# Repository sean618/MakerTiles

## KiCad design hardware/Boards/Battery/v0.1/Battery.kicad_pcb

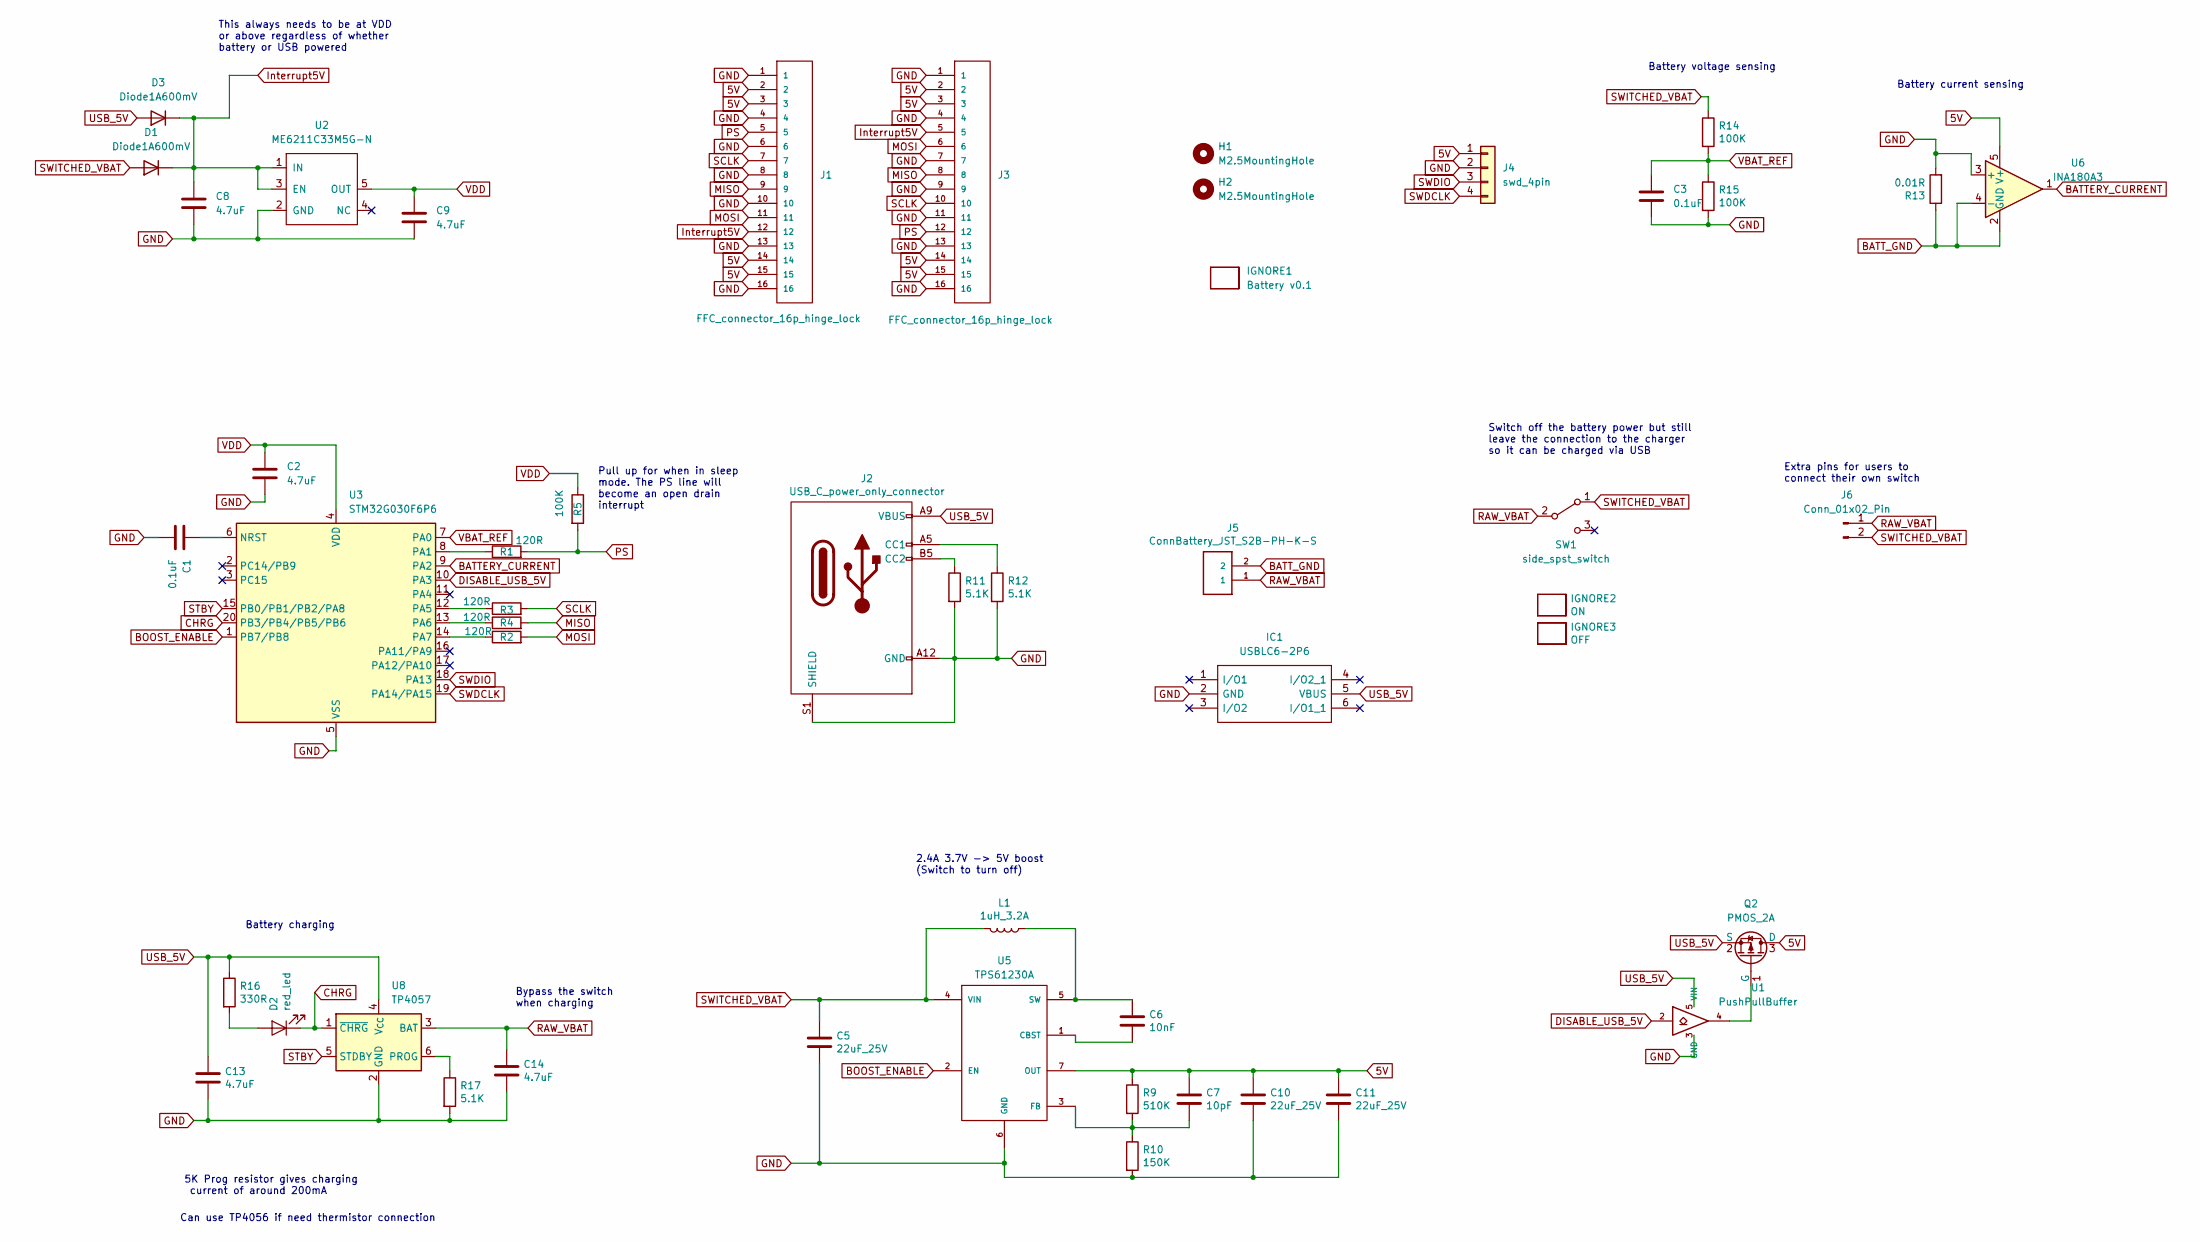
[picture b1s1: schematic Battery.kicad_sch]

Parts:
C1, C3: 0.1uF; C_0402_1005Metric
C2, C8, C9, C13, C14: 4.7uF; C_0402_1005Metric
C5, C10, C11: 22uF_25V; C_0805_2012Metric
C6: 10nF; C_0402_1005Metric
C7: 10pF; C_0402_1005Metric
D1, D3: Diode1A600mV; D_SOD-323
D2: red_led; LED_SML-D12D1WT86; Manufacturer_Part_Number SML-D12D1WT86
H1, H2: M2.5MountingHole; MountingHole_2.7mm_M2.5_ISO7380
IC1: USBLC6-2P6; Manufacturer_Part_Number USBLC6-2P6
IGNORE1: Battery v0.1; BoardText
IGNORE2: ON; BoardText
IGNORE3: OFF; BoardText
J1, J3: FFC_connector_16p_hinge_lock
J2: USB_C_power_only_connector; USB_C_Receptacle_power_only_6P
J4: swd_4pin; swd_header
J5: ConnBattery_JST_S2B-PH-K-S; JST_PH_S2B-PH-K_1x02_P2.00mm_Horizontal; Manufacturer_Part_Number S2B-PH-K-S
J6: Conn_01x02_Pin; PinHeader_1x02_P2.54mm_Vertical
L1: 1uH_3.2A; L_1008_2520Metric
Q2: PMOS_2A; SOT-23
R1, R2, R3, R4: 120R; R_0402_1005Metric
R5, R14, R15: 100K; R_0402_1005Metric
R9: 510K; R_0402_1005Metric
R10: 150K; R_0402_1005Metric
R11, R12, R17: 5.1K; R_0402_1005Metric
R13: 0.01R; R_0603_1608Metric_Pad0.98x0.95mm_HandSolder
R16: 330R; R_0402_1005Metric
SW1: side_spst_switch
U1: PushPullBuffer; 74LVC1G07GW
U2: ME6211C33M5G-N; SOT-23-5
U3: STM32G030F6P6; TSSOP-20_4.4x6.5mm_P0.65mm
U5: TPS61230A
U6: INA180A3; SOT-23-5
U8: TP4057; SOT-23-6

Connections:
5V: C7.1, C10.1, C11.1, J1.2, J1.3, J1.14, J1.15, J3.2, J3.3, J3.14, J3.15, J4.1, Q2.3 (D), R9.1, U5.7 (OUT), U6.5 (V+)
BATTERY_CURRENT: U3.9 (PA2), U6.1
BATT_GND: J5.2, R13.1, U6.2 (GND), U6.4 (-)
BOOST_ENABLE: U3.1 (PB7/PB8), U5.2 (EN)
CHRG: D2.1 (K), U3.20 (PB3/PB4/PB5/PB6), U8.1 (~CHRG)
DISABLE_USB_5V: U1.2, U3.10 (PA3)
GND: C1.2, C2.2, C3.2, C5.2, C8.2, C9.2, C10.2, C11.2, C13.2, C14.2, IC1.2 (GND), J1.1, J1.4, J1.6, J1.8, J1.10, J1.13, J1.16, J2.A12 (GND), J2.B12 (GND), J2.S1 (SHIELD), J3.1, J3.4, J3.7, J3.9, J3.11, J3.13, J3.16, J4.2, R10.2, R11.2, R12.2, R13.2, R15.2, R17.2, U1.3 (GND), U2.2 (GND), U3.5 (VSS), U5.6 (GND), U6.3 (+), U8.2 (GND)
Interrupt5V: C8.1, D1.1 (K), D3.1 (K), J1.12, J3.5, U2.1 (IN), U2.3 (EN)
MISO: J1.9, J3.8, R4.2
MOSI: J1.11, J3.6, R2.2
unnamed: D2.2 (A), R16.2
unnamed: J2.A5 (CC1), R12.1
unnamed: J2.B5 (CC2), R11.1
unnamed: Q2.1 (G), U1.4
unnamed: C1.1, U3.6 (NRST)
unnamed: R1.1, U3.8 (PA1)
unnamed: R3.1, U3.12 (PA5)
unnamed: R4.1, U3.13 (PA6)
unnamed: R2.1, U3.14 (PA7)
unnamed: C6.2, U5.1 (CBST)
unnamed: C7.2, R9.2, R10.1, U5.3 (FB)
unnamed: C6.1, L1.1, U5.5 (SW)
unnamed: R17.1, U8.6 (PROG)
PS: J1.5, J3.12, R1.2, R5.2
RAW_VBAT: C14.1, J5.1, J6.1, SW1.2 (B), U8.3 (BAT)
SCLK: J1.7, J3.10, R3.2
STBY: U3.15 (PB0/PB1/PB2/PA8), U8.5 (STDBY)
SWDCLK: J4.4, U3.19 (PA14/PA15)
SWDIO: J4.3, U3.18 (PA13)
SWITCHED_VBAT: C5.1, D1.2 (A), J6.2, L1.2, R14.1, SW1.1 (A), U5.4 (VIN)
USB_5V: C13.1, D3.2 (A), IC1.5 (VBUS), J2.A9 (VBUS), J2.B9 (VBUS), Q2.2 (S), R16.1, U1.5 (VIN), U8.4 (V_{CC})
VBAT_REF: C3.1, R14.2, R15.1, U3.7 (PA0)
VDD: C2.1, C9.1, R5.1, U2.5 (OUT), U3.4 (VDD)

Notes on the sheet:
Battery current sensing
This always needs to be at VDD or above regardless of whether battery or USB powered
Can use TP4056 if need thermistor connection
Bypass the switch when charging
Battery charging
Extra pins for users to connect their own switch
Switch off the battery power but still leave the connection to the charger so it can be charged via USB
Pull up for when in sleep mode. The PS line will become an open drain interrupt
Battery voltage sensing
5K Prog resistor gives charging current of around 200mA
2.4A 3.7V -> 5V boost (Switch to turn off)

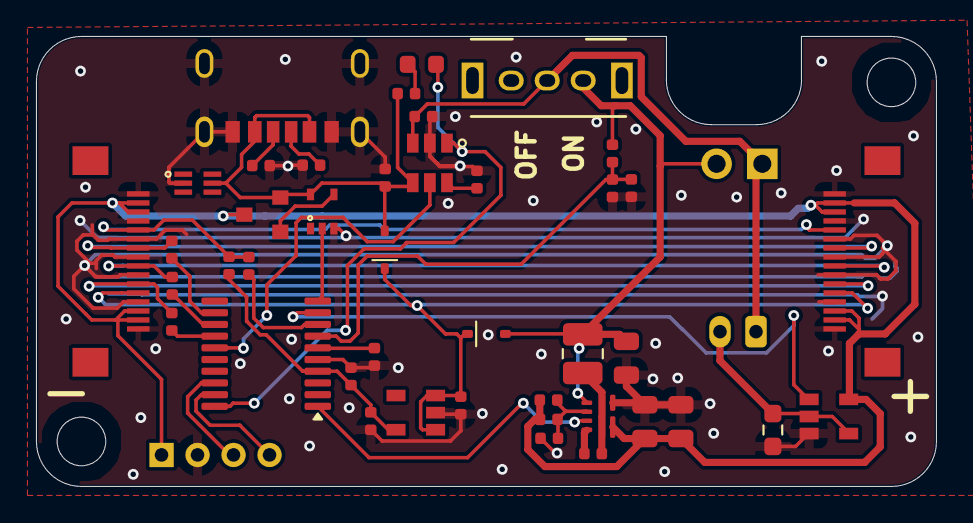
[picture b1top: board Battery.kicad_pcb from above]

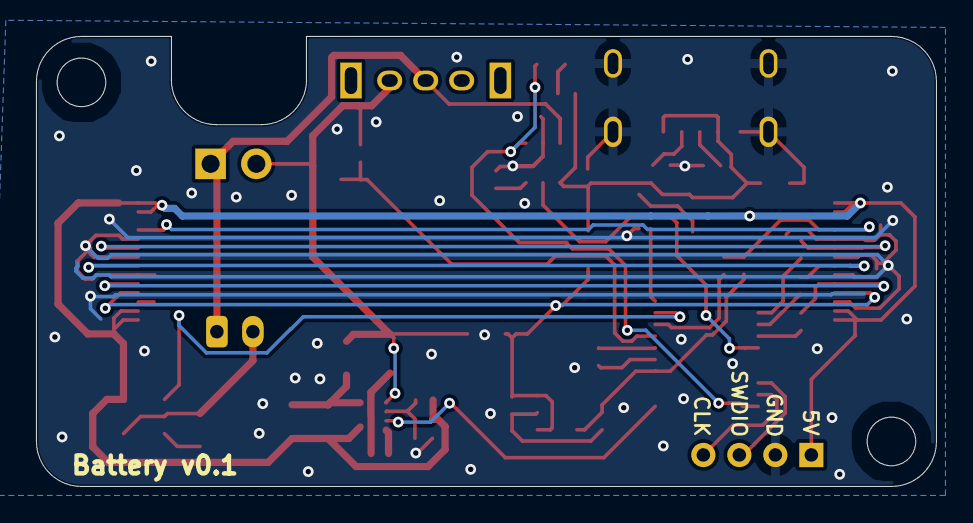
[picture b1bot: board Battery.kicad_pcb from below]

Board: 4 copper layers, 50.0 x 25.0 mm, 50 parts (2 on the bottom side), 33 nets.

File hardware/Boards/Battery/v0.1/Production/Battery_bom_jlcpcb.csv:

Comment,Designator,Footprint,LCSC Part Number
4.7uF,"C9,C13,C14,C8,C2",C_0402_1005Metric,C23733
FFC_connector_16p_hinge_lock,"J1,J3",FFC_connector_16p_hinge_lock,C262665
0.01R,R13,R_0603_1608Metric_Pad0.98x0.95mm_HandSolder,C158899
Diode1A600mV,"D1,D3",D_SOD-323,C191023
22uF_25V,"C10,C5,C11",C_0805_2012Metric,C602037
red_led,D2,LED_SML-D12D1WT86,C2286
side_spst_switch,SW1,side_spst_switch,C431548
10pF,C7,C_0402_1005Metric,C32949
ConnBattery_JST_S2B-PH-K-S,J5,JST_PH_S2B-PH-K_1x02_P2.00mm_Horizontal,C173752
USB_C_power_only_connector,J2,USB_C_Receptacle_power_only_6P,C283540
INA180A3,U6,SOT-23-5,C122882
USBLC6-2P6,IC1,USBLC6-2P6,C2827693
TP4057,U8,SOT-23-6,C5380673
TPS61230A,U5,TPS61230A,C376005
ME6211C33M5G-N,U2,SOT-23-5,C81233
150K,R10,R_0402_1005Metric,C25755
510K,R9,R_0402_1005Metric,C11616
100K,"R5,R15,R14",R_0402_1005Metric,C25741
330R,R16,R_0402_1005Metric,C25104
120R,"R2,R3,R4,R1",R_0402_1005Metric,C25079
PMOS_2A,Q2,SOT-23,C306862
STM32G030F6P6,U3,TSSOP-20_4.4x6.5mm_P0.65mm,C529330
5.1K,"R12,R17,R11",R_0402_1005Metric,C25905
1uH_3.2A,L1,L_1008_2520Metric,C315711
0.1uF,"C1,C3",C_0402_1005Metric,C1525
10nF,C6,C_0402_1005Metric,C15195
PushPullBuffer,U1,74LVC1G07GW,C426705

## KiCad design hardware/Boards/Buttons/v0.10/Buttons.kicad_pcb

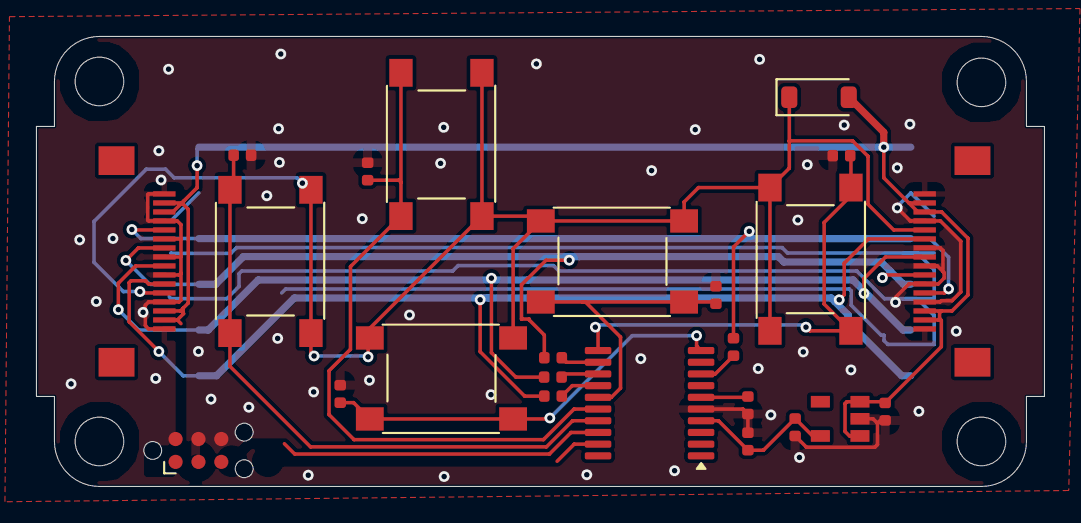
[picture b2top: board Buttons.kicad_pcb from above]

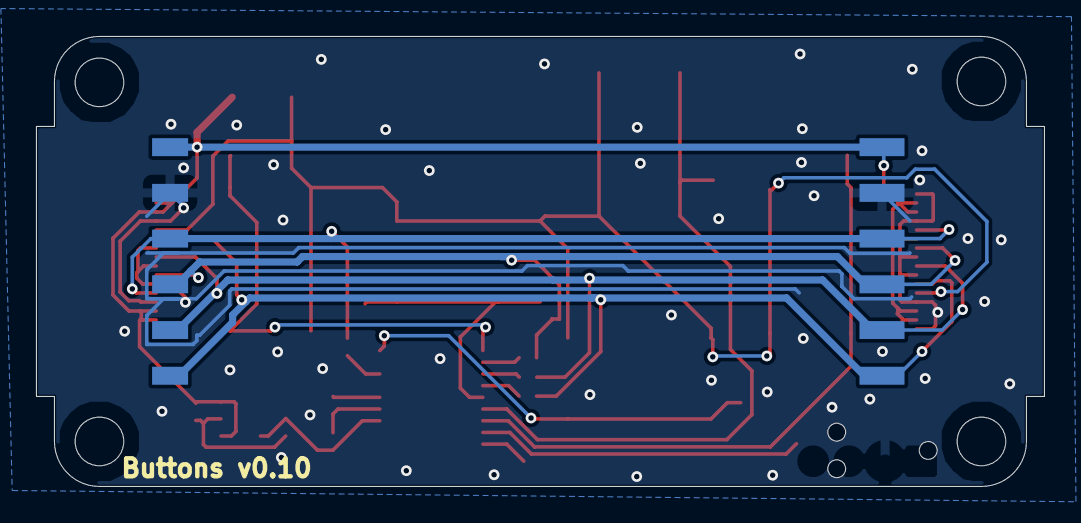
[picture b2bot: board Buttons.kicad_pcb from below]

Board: 2 copper layers, 56.0 x 25.0 mm, 31 parts (2 on the bottom side), 20 nets.

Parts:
C1: 0.1uF; C_0402_1005Metric
C2, C8, C9: 4.7uF; C_0402_1005Metric
D2: 1N4148W; D_SOD-123
H1, H2, H3, H4: M2.5MountingHole; MountingHole_2.7mm_M2.5_ISO7380
IGNORE1: Buttons v0.10; BoardText
J1: 01x06_2.54mm_Male
J2: 01x06_2.54mm_Female
J3, J5: FFC_connector_16p_hinge_lock
J4: Conn_ARM_SWD_TagConnect_TC2030-NL; Tag-Connect_TC2030-IDC-NL_2x03_P1.27mm_Vertical
R1, R2, R3, R4: 75R; R_0402_1005Metric
R5, R6, R7, R8, R9: 10K; R_0402_1005Metric
SW1, SW2, SW3, SW4, SW6: button_6x6x7; SW_SPST_PTS645
U2: ME6211C33M5G-N; SOT-23-5
U3: STM32G030F6P6; TSSOP-20_4.4x6.5mm_P0.65mm

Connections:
5V: C8.1, D2.2 (A), J1.1, J2.6, J3.2, J3.3, J3.14, J3.15, J5.2, J5.3, J5.14, J5.15, U2.1 (IN), U2.3 (EN)
GND: C1.2, C2.2, C8.2, C9.2, J1.2, J2.5, J3.1, J3.4, J3.6, J3.8, J3.10, J3.13, J3.16, J4.5 (GND), J5.1, J5.4, J5.6, J5.8, J5.10, J5.13, J5.16, R5.1, R6.1, R7.1, R8.1, R9.1, U2.2 (GND), U3.5 (VSS)
Interrupt5V: D2.1 (K), J3.12, J5.12, SW1.2, SW2.2, SW3.2, SW4.2, SW6.2
MISO: J1.5, J2.2, J3.9, J5.9, R4.2
MOSI: J1.6, J2.1, J3.11, J5.11, R2.2
NRST: C1.1, J4.3 (~RESET), U3.6 (NRST)
unnamed: R1.1, U3.8 (PA1)
unnamed: R3.1, U3.12 (PA5)
unnamed: R4.1, U3.13 (PA6)
unnamed: R2.1, U3.14 (PA7)
PS: J1.3, J2.4, J3.5, J5.5, R1.2
SCLK: J1.4, J2.3, J3.7, J5.7, R3.2
SW1: R5.2, SW2.1, U3.16 (PA11/PA9)
SW2: R6.2, SW1.1, U3.17 (PA12/PA10)
SW3: R7.2, SW6.1, U3.11 (PA4)
SW4: R9.2, SW3.1, U3.15 (PB0/PB1/PB2/PA8)
SW5: R8.2, SW4.1, U3.10 (PA3)
SWDCLK: J4.4 (SWCLK), U3.19 (PA14/PA15)
SWDIO: J4.2 (SWDIO), U3.18 (PA13)
VDD: C2.1, C9.1, J4.1 (VCC), U2.5 (OUT), U3.4 (VDD)

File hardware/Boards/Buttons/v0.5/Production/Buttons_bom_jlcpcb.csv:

Comment,Designator,Footprint,LCSC Part Number
4.7uF,"C9,C8,C2",C_0402_1005Metric,C23733
FFC_connector_16p_hinge_lock,"J5,J3",FFC_connector_16p_hinge_lock,C262665
button_6x6x7,"SW1,SW2,SW4,SW3,SW6",SW_SPST_PTS645,C381064
10K,"R9,R6,R8,R5,R7",R_0402_1005Metric,C25744
ME6211C33M5G-N,U2,SOT-23-5,C81233
75R,"R2,R3,R4,R1",R_0402_1005Metric,C25133
STM32G030F6P6,U3,TSSOP-20_4.4x6.5mm_P0.65mm,C529330
0.1uF,C1,C_0402_1005Metric,C1525
1N4148W,D2,D_SOD-123,C81598
01x06_2.54mm_Male,J1,01x06_2.54mm_Male,C5242199
01x06_2.54mm_Female,J2,01x06_2.54mm_Female,C5142239

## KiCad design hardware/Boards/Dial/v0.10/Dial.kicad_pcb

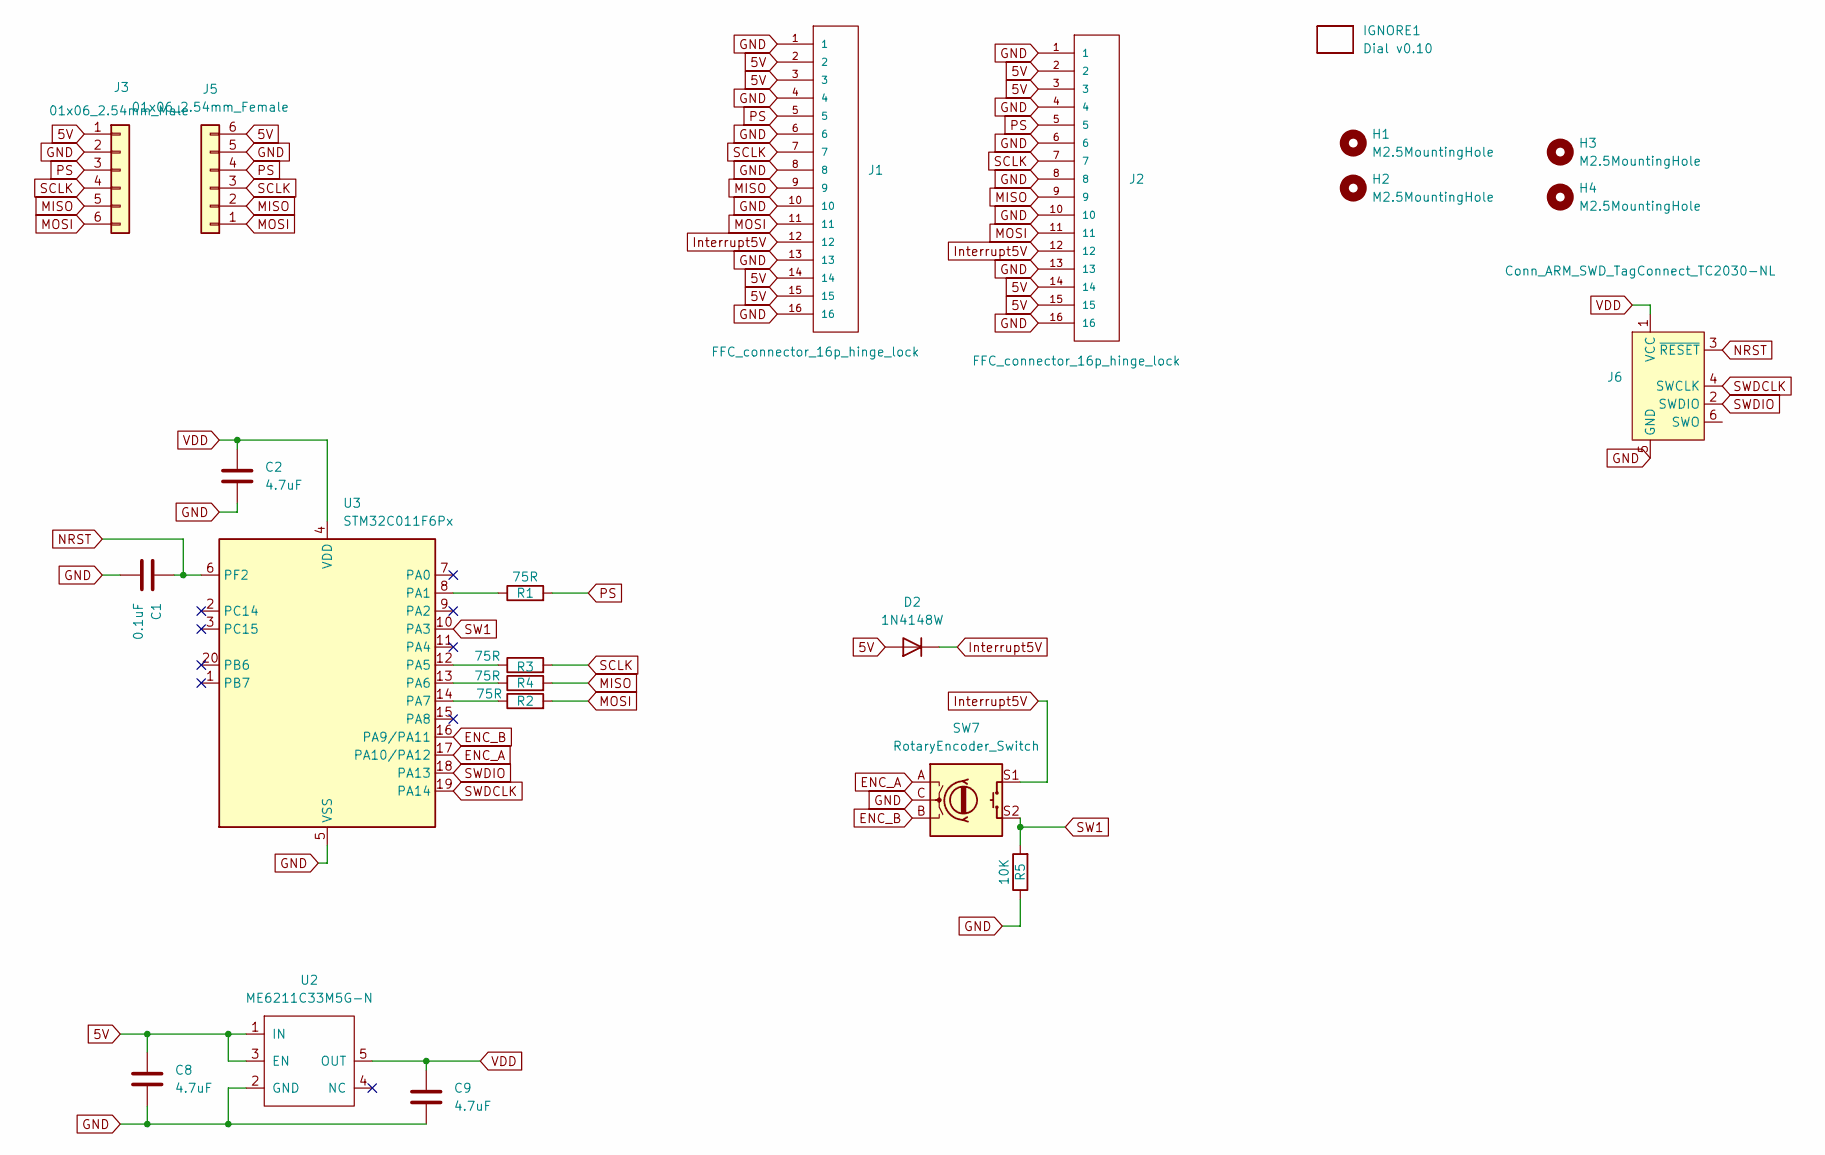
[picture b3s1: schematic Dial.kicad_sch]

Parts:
C1: 0.1uF; C_0402_1005Metric
C2, C8, C9: 4.7uF; C_0402_1005Metric
D2: 1N4148W; D_SOD-123
H1, H2, H3, H4: M2.5MountingHole; MountingHole_2.7mm_M2.5_ISO7380
IGNORE1: Dial v0.10; BoardText
J1, J2: FFC_connector_16p_hinge_lock
J3: 01x06_2.54mm_Male
J5: 01x06_2.54mm_Female
J6: Conn_ARM_SWD_TagConnect_TC2030-NL; Tag-Connect_TC2030-IDC-NL_2x03_P1.27mm_Vertical
R1, R2, R3, R4: 75R; R_0402_1005Metric
R5: 10K; R_0402_1005Metric
SW7: RotaryEncoder_Switch; RotaryEncoderEC12D
U2: ME6211C33M5G-N; SOT-23-5
U3: STM32C011F6Px; TSSOP-20_4.4x6.5mm_P0.65mm

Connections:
5V: C8.1, D2.2 (A), J1.2, J1.3, J1.14, J1.15, J2.2, J2.3, J2.14, J2.15, J3.1, J5.6, U2.1 (IN), U2.3 (EN)
ENC_A: SW7.A, U3.17 (PA10/PA12)
ENC_B: SW7.B, U3.16 (PA9/PA11)
GND: C1.2, C2.2, C8.2, C9.2, J1.1, J1.4, J1.6, J1.8, J1.10, J1.13, J1.16, J2.1, J2.4, J2.6, J2.8, J2.10, J2.13, J2.16, J3.2, J5.5, J6.5 (GND), R5.1, SW7.C, U2.2 (GND), U3.5 (VSS)
Interrupt5V: D2.1 (K), J1.12, J2.12, SW7.S1
MISO: J1.9, J2.9, J3.5, J5.2, R4.2
MOSI: J1.11, J2.11, J3.6, J5.1, R2.2
NRST: C1.1, J6.3 (~RESET), U3.6 (PF2)
unnamed: R1.1, U3.8 (PA1)
unnamed: R3.1, U3.12 (PA5)
unnamed: R4.1, U3.13 (PA6)
unnamed: R2.1, U3.14 (PA7)
PS: J1.5, J2.5, J3.3, J5.4, R1.2
SCLK: J1.7, J2.7, J3.4, J5.3, R3.2
SW1: R5.2, SW7.S2, U3.10 (PA3)
SWDCLK: J6.4 (SWCLK), U3.19 (PA14)
SWDIO: J6.2 (SWDIO), U3.18 (PA13)
VDD: C2.1, C9.1, J6.1 (VCC), U2.5 (OUT), U3.4 (VDD)

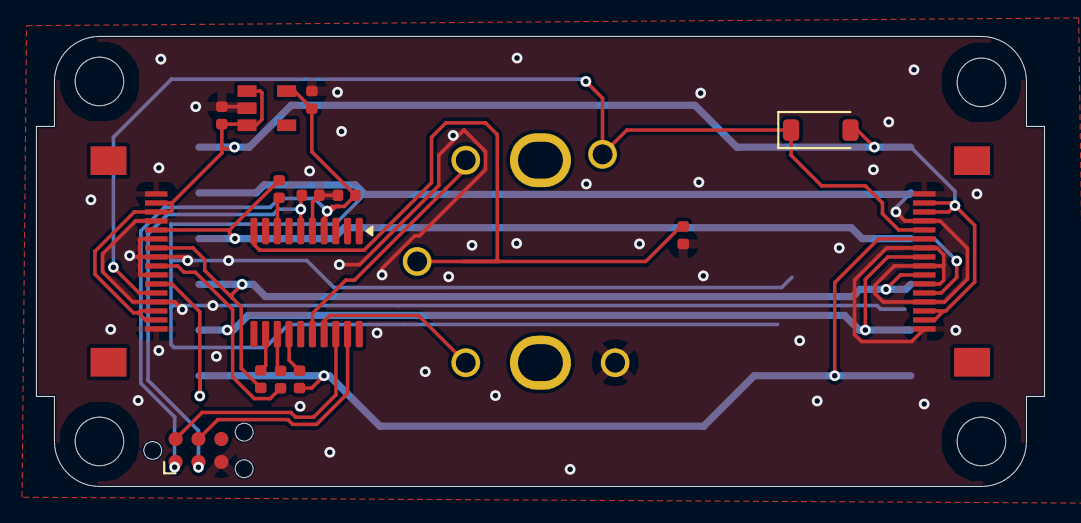
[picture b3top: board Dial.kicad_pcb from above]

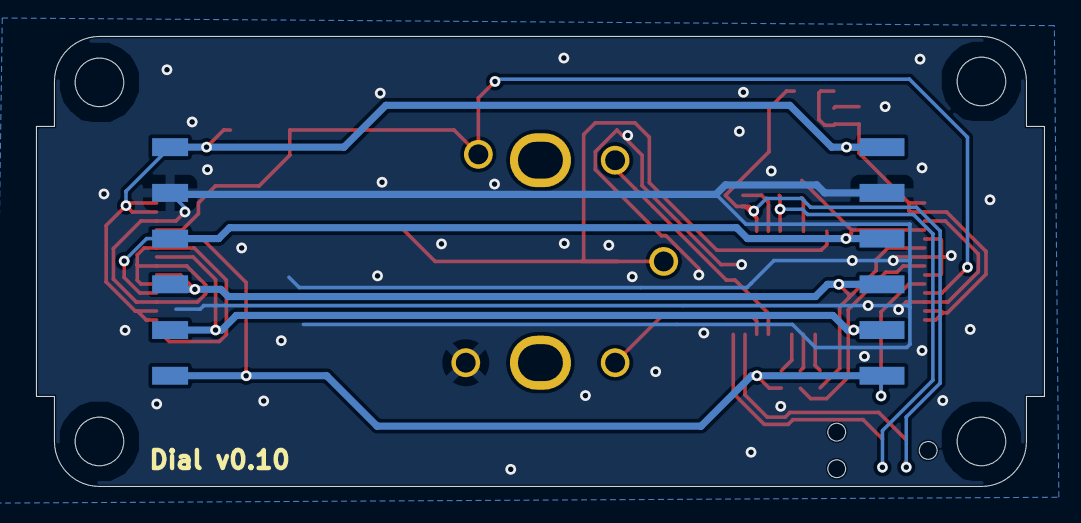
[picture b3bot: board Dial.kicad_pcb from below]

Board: 2 copper layers, 56.0 x 25.0 mm, 23 parts (2 on the bottom side), 18 nets.

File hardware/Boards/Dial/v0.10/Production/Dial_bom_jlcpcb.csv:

Comment,Designator,Footprint,LCSC Part Number
4.7uF,"C9,C8,C2",C_0402_1005Metric,C23733
FFC_connector_16p_hinge_lock,"J1,J2",FFC_connector_16p_hinge_lock,C262665
STM32C011F6Px,U3,TSSOP-20_4.4x6.5mm_P0.65mm,C5456198
1N4148W,D2,D_SOD-123,C81598
ME6211C33M5G-N,U2,SOT-23-5,C81233
75R,"R2,R4,R1,R3",R_0402_1005Metric,C25133
RotaryEncoder_Switch,SW7,RotaryEncoderEC12D,C112349
10K,R5,R_0402_1005Metric,C25744
0.1uF,C1,C_0402_1005Metric,C1525
01x06_2.54mm_Female,J5,01x06_2.54mm_Female,C5142239
01x06_2.54mm_Male,J3,01x06_2.54mm_Male,C5242199
